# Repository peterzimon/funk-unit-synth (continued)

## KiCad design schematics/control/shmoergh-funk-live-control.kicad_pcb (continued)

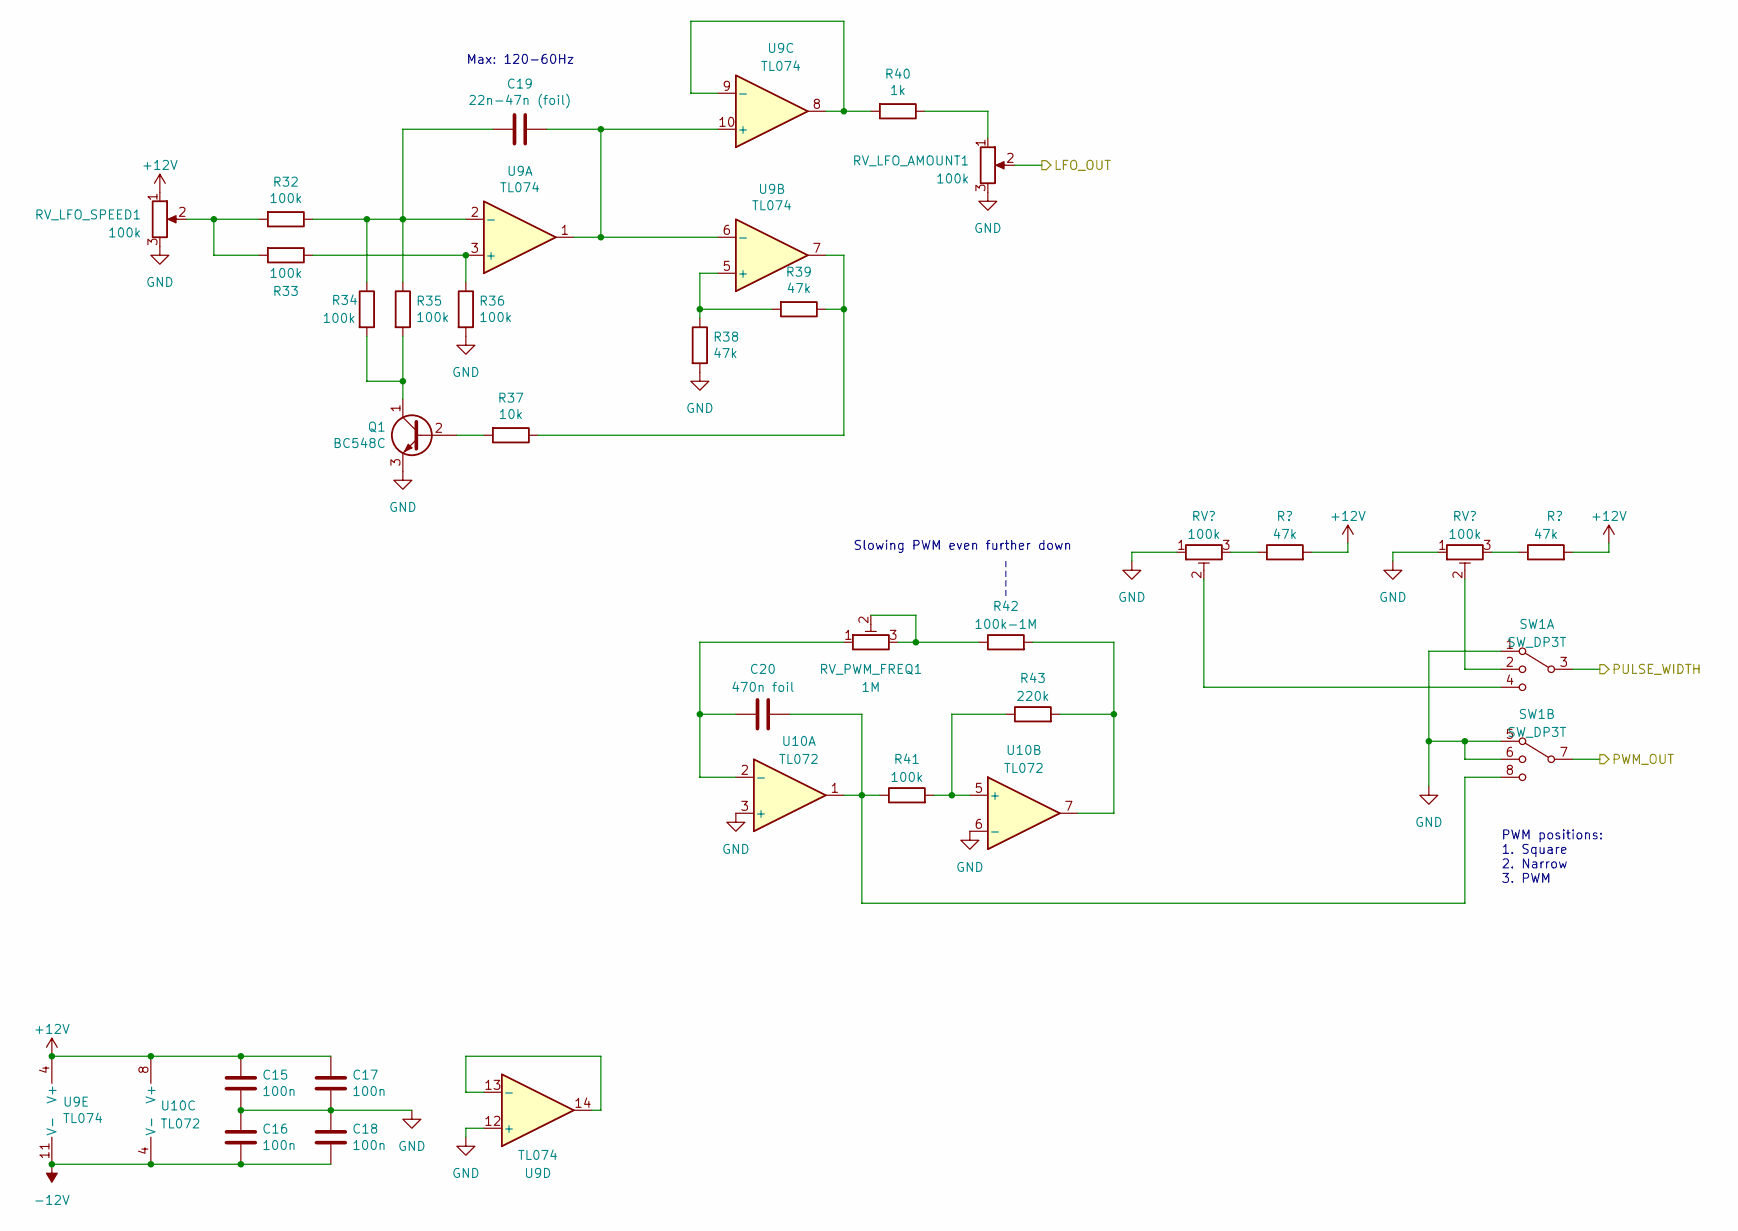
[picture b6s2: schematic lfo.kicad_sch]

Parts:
C15, C16, C17, C18: 100n; C_Disc_D3.0mm_W2.0mm_P2.50mm
C19: 22n-47n (foil); C_Rect_L7.0mm_W3.5mm_P5.00mm
C20: 470n foil; C_Rect_L7.0mm_W3.5mm_P5.00mm
Q1: BC548C; TO-92_Inline_Wide
R32, R33, R34, R35, R36, R41: 100k; R_Axial_DIN0207_L6.3mm_D2.5mm_P7.62mm_Horizontal
R37: 10k; R_Axial_DIN0207_L6.3mm_D2.5mm_P7.62mm_Horizontal
R38, R39, R44, R45: 47k; R_Axial_DIN0207_L6.3mm_D2.5mm_P7.62mm_Horizontal
R40: 1k; R_Axial_DIN0207_L6.3mm_D2.5mm_P7.62mm_Horizontal
R42: 100k-1M; R_Axial_DIN0207_L6.3mm_D2.5mm_P7.62mm_Horizontal
R43: 220k; R_Axial_DIN0207_L6.3mm_D2.5mm_P7.62mm_Horizontal
RV_LFO_AMOUNT1: 100k; NSL25_01x03_Vertical
RV_LFO_SPEED1: 100k; NSL25_01x03_Vertical
RV_NARROW_BIAS1: 100k; Potentiometer_Runtron_RM-065_Vertical
RV_PWM_BIAS1: 100k; Potentiometer_Runtron_RM-065_Vertical
RV_PWM_FREQ1: 1M; Potentiometer_Runtron_RM-065_Vertical
SW1: SW_DP3T; NSL25_01x08_Vertical
U9: TL074; DIP-14_W7.62mm_LongPads
U10: TL072; DIP-8_W7.62mm_LongPads

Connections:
-12V: C16.2, C18.2, U9.11 (V-), U10.4 (V-); also elsewhere on the board
unnamed: Q1.2 (B), R37.2
unnamed: Q1.1 (C), R34.2, R35.2
unnamed: R32.2, R33.2, RV_LFO_SPEED1.2
unnamed: R37.1, R39.1, U9.7
unnamed: R40.1, RV_LFO_AMOUNT1.1
unnamed: R42.1, RV_PWM_FREQ1.2, RV_PWM_FREQ1.3
unnamed: R42.2, R43.2, U10.7
unnamed: R44.1, RV_PWM_BIAS1.3
unnamed: R45.1, RV_NARROW_BIAS1.3
unnamed: R33.1, R36.1, U9.3 (+)
unnamed: C19.2, R32.1, R34.1, R35.1, U9.2 (-)
unnamed: R38.1, R39.2, U9.5 (+)
unnamed: C19.1, U9.1, U9.6 (-), U9.10 (+)
unnamed: R40.2, U9.8, U9.9 (-)
unnamed: U9.13 (-), U9.14
unnamed: C20.1, RV_PWM_FREQ1.1, U10.2 (-)
unnamed: R41.2, R43.1, U10.5 (+)
PWM_LFO: C20.2, R41.1, SW1.8, U10.1; also elsewhere on the board
PWM_LFO_BIAS: RV_PWM_BIAS1.2, SW1.4; also elsewhere on the board
PWM_NARROW_BIAS: RV_NARROW_BIAS1.2, SW1.2; also elsewhere on the board

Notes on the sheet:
Max: 120-60Hz
PWM positions: 1. Square 2. Narrow 3. PWM
Slowing PWM even further down

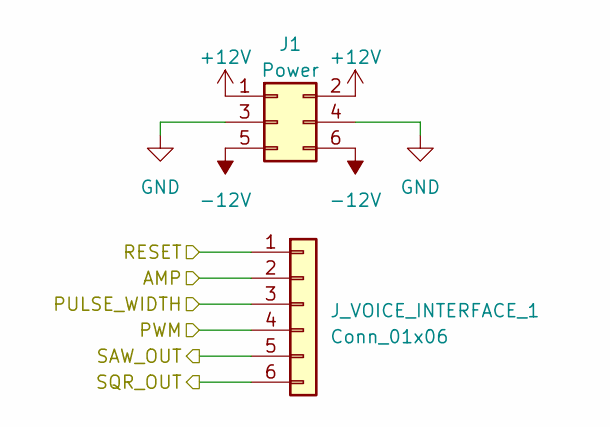
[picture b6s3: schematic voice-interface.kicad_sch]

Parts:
J1: Power; PinHeader_2x03_P2.54mm_Vertical
J_VOICE_INTERFACE_1: Conn_01x06; PinHeader_1x06_P2.54mm_Vertical

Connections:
-12V: J1.5, J1.6; also elsewhere on the board
/Digital/AMP_1: J_VOICE_INTERFACE_1.2; also elsewhere on the board
/Digital/RESET_1: J_VOICE_INTERFACE_1.1; also elsewhere on the board
/LFO + PWM/PULSE_WIDTH: J_VOICE_INTERFACE_1.3; also elsewhere on the board
/LFO + PWM/PWM_OUT: J_VOICE_INTERFACE_1.4; also elsewhere on the board
/Mixer/SAW_1_IN: J_VOICE_INTERFACE_1.5; also elsewhere on the board
/Mixer/SQR_1_IN: J_VOICE_INTERFACE_1.6; also elsewhere on the board

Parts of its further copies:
J2, J3, J4, J5, J6: Power; PinHeader_2x03_P2.54mm_Vertical
J_VOICE_INTERFACE_2, J_VOICE_INTERFACE_3, J_VOICE_INTERFACE_4, J_VOICE_INTERFACE_5, J_VOICE_INTERFACE_6: Conn_01x06; PinHeader_1x06_P2.54mm_Vertical

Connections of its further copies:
-12V: J2.5, J2.6, J3.5, J3.6, J4.5, J4.6, J5.5, J5.6, J6.5, J6.6; also elsewhere on the board
/Digital/AMP_2: J_VOICE_INTERFACE_2.2; also elsewhere on the board
/Digital/AMP_3: J_VOICE_INTERFACE_3.2; also elsewhere on the board
/Digital/AMP_4: J_VOICE_INTERFACE_4.2; also elsewhere on the board
/Digital/AMP_5: J_VOICE_INTERFACE_5.2; also elsewhere on the board
/Digital/AMP_6: J_VOICE_INTERFACE_6.2; also elsewhere on the board
/Digital/RESET_2: J_VOICE_INTERFACE_2.1; also elsewhere on the board
/Digital/RESET_3: J_VOICE_INTERFACE_3.1; also elsewhere on the board
/Digital/RESET_4: J_VOICE_INTERFACE_4.1; also elsewhere on the board
/Digital/RESET_5: J_VOICE_INTERFACE_5.1; also elsewhere on the board
/Digital/RESET_6: J_VOICE_INTERFACE_6.1; also elsewhere on the board
/LFO + PWM/PULSE_WIDTH: J_VOICE_INTERFACE_2.3, J_VOICE_INTERFACE_3.3, J_VOICE_INTERFACE_4.3, J_VOICE_INTERFACE_5.3, J_VOICE_INTERFACE_6.3; also elsewhere on the board
/LFO + PWM/PWM_OUT: J_VOICE_INTERFACE_2.4, J_VOICE_INTERFACE_3.4, J_VOICE_INTERFACE_4.4, J_VOICE_INTERFACE_5.4, J_VOICE_INTERFACE_6.4; also elsewhere on the board
/Mixer/SAW_2_IN: J_VOICE_INTERFACE_2.5; also elsewhere on the board
/Mixer/SAW_3_IN: J_VOICE_INTERFACE_3.5; also elsewhere on the board
/Mixer/SAW_4_IN: J_VOICE_INTERFACE_4.5; also elsewhere on the board
/Mixer/SAW_5_IN: J_VOICE_INTERFACE_5.5; also elsewhere on the board
/Mixer/SAW_6_IN: J_VOICE_INTERFACE_6.5; also elsewhere on the board
/Mixer/SQR_2_IN: J_VOICE_INTERFACE_2.6; also elsewhere on the board
/Mixer/SQR_3_IN: J_VOICE_INTERFACE_3.6; also elsewhere on the board
/Mixer/SQR_4_IN: J_VOICE_INTERFACE_4.6; also elsewhere on the board
/Mixer/SQR_5_IN: J_VOICE_INTERFACE_5.6; also elsewhere on the board
/Mixer/SQR_6_IN: J_VOICE_INTERFACE_6.6; also elsewhere on the board

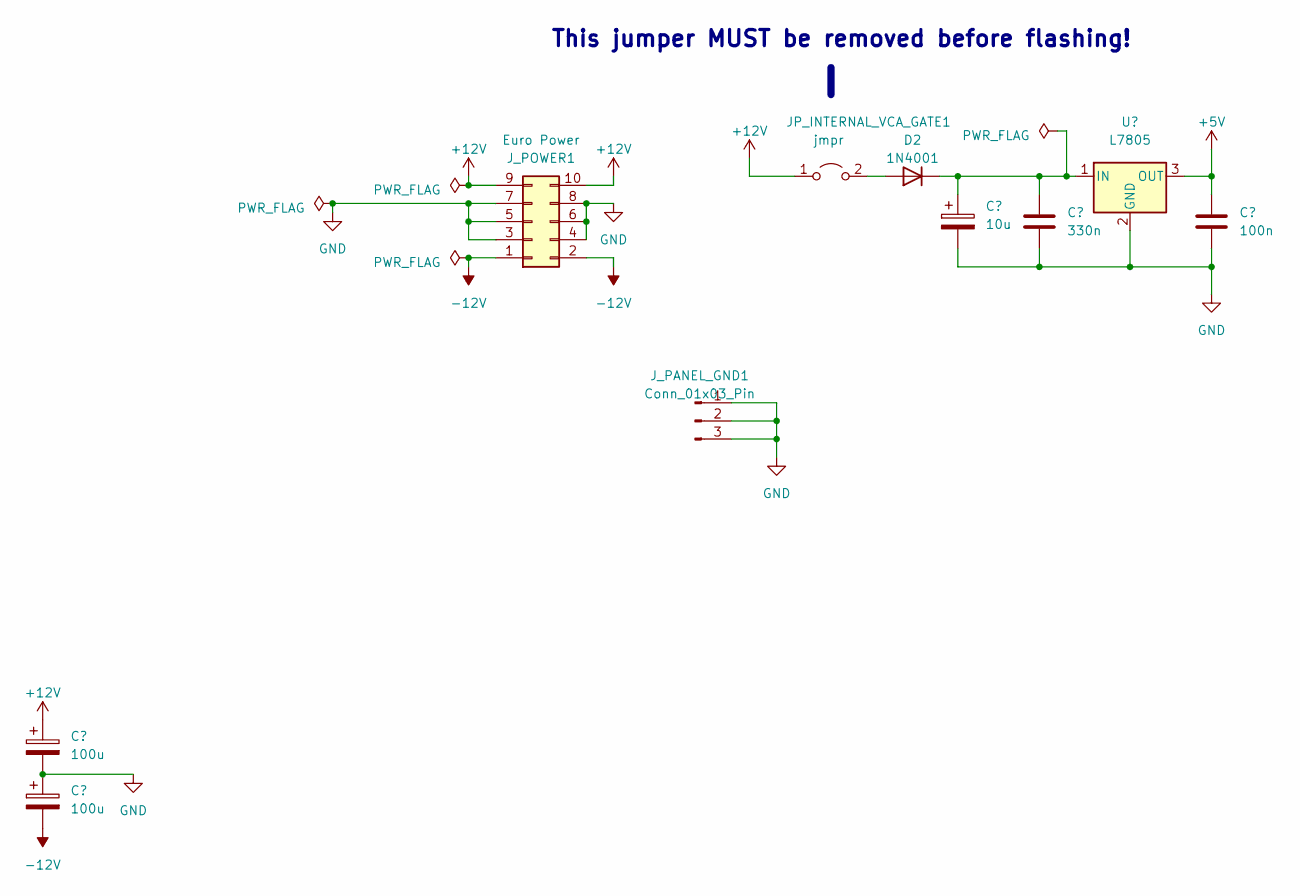
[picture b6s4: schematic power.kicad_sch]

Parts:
C21, C22: 100u; CP_Radial_D6.3mm_P2.50mm
C23: 10u; CP_Radial_D6.3mm_P2.50mm
C24: 330n; C_Disc_D3.0mm_W2.0mm_P2.50mm
C25: 100n; C_Disc_D3.0mm_W2.0mm_P2.50mm
D2: 1N4001; D_DO-41_SOD81_P7.62mm_Horizontal
JP_INTERNAL_VCA_GATE1: jmpr; Jumper_P2.54mm_D0.7mm
J_PANEL_GND1: Conn_01x03_Pin; NSL25_01x03_Vertical
J_POWER1: Euro Power; IDC-Header_2x05_P2.54mm_Vertical
U11: L7805; TO-220-3_Vertical

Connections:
+5V: C25.1, U11.3 (OUT); also elsewhere on the board
-12V: C22.2, J_POWER1.1, J_POWER1.2; also elsewhere on the board
unnamed: C23.1, C24.1, D2.1 (K), U11.1 (IN)

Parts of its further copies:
JP_MCU_EXT_PWR2: jmpr; Jumper_P2.54mm_D0.7mm

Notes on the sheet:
This jumper MUST be removed before flashing!

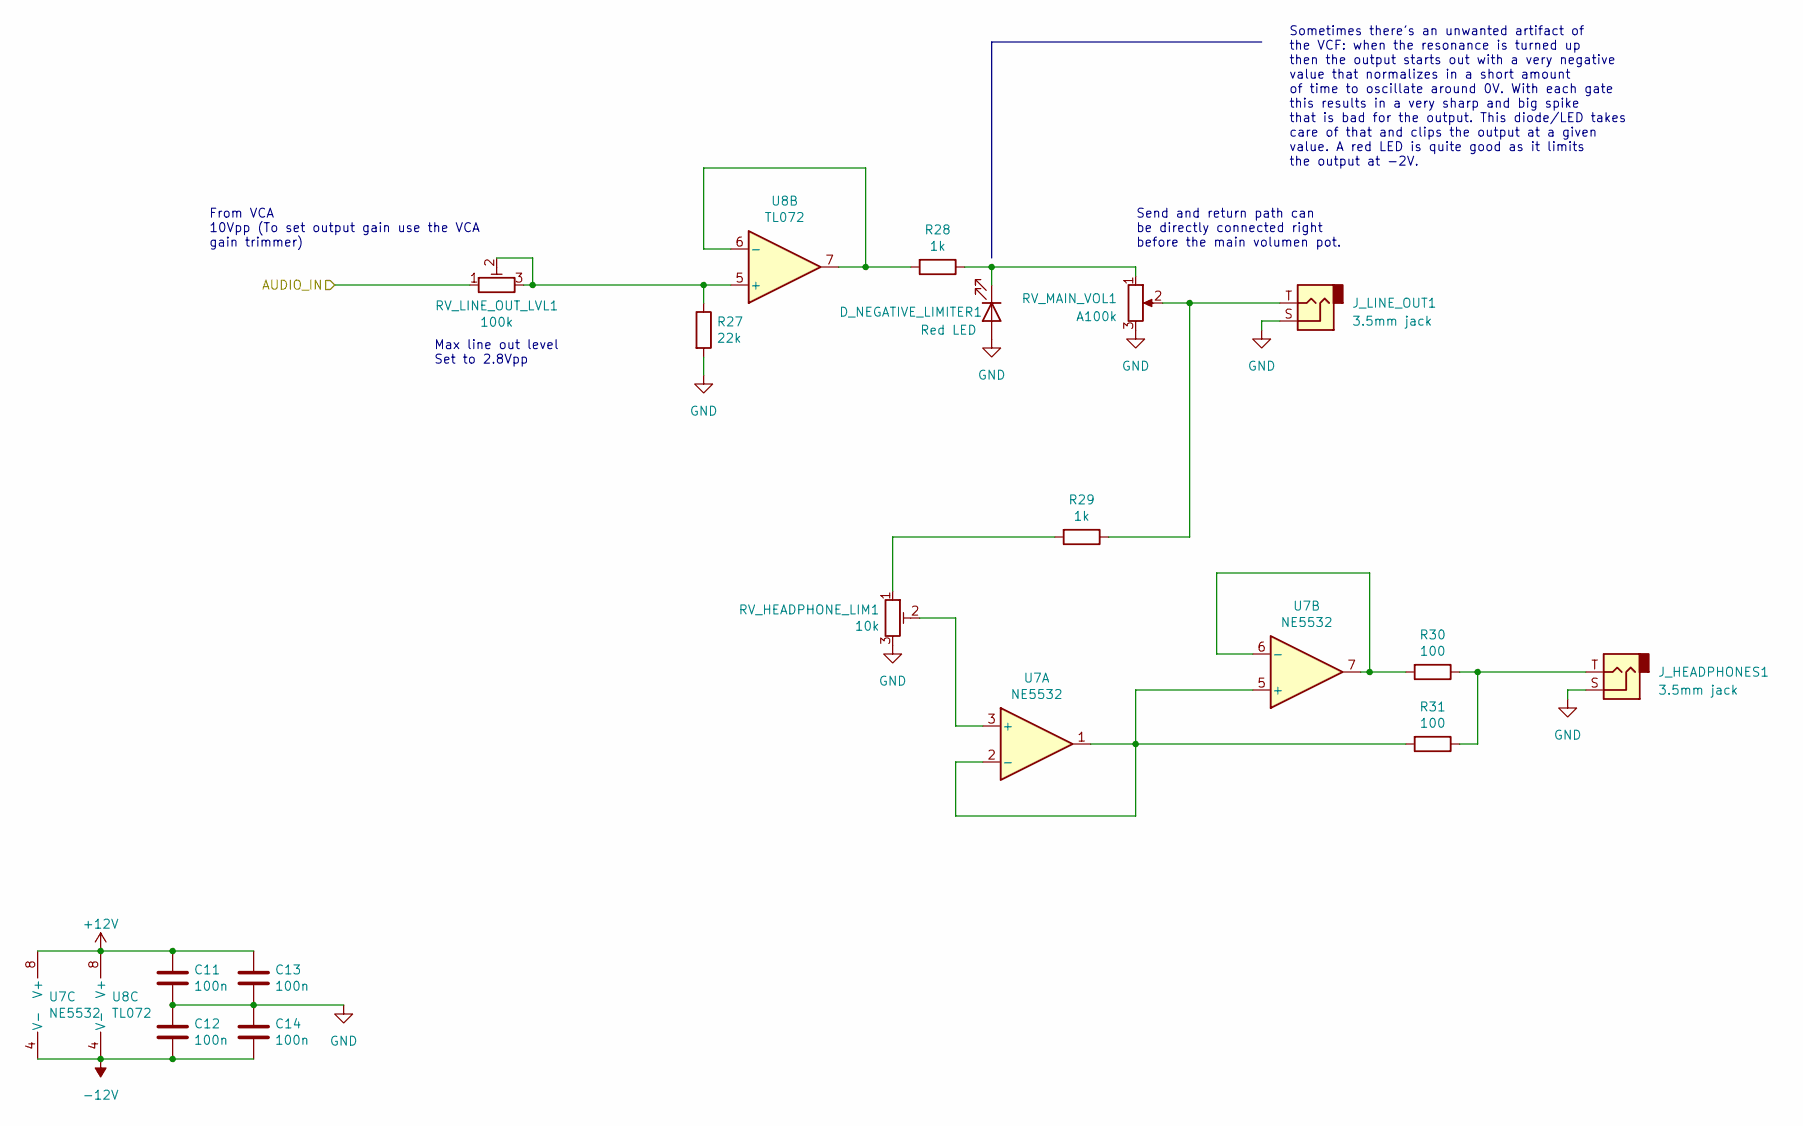
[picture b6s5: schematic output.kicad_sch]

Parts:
C11, C12, C13, C14: 100n; C_Disc_D3.0mm_W2.0mm_P2.50mm
D_NEGATIVE_LIMITER1: Red LED; LED_D5.0mm
J_HEADPHONES1: 3.5mm jack; NSL25_01x02_Vertical-AudioJack-TS
J_LINE_OUT1: 3.5mm jack; NSL25_01x02_Vertical-AudioJack-TS
R27: 22k; R_Axial_DIN0207_L6.3mm_D2.5mm_P7.62mm_Horizontal
R28, R29: 1k; R_Axial_DIN0207_L6.3mm_D2.5mm_P7.62mm_Horizontal
R30, R31: 100; R_Axial_DIN0207_L6.3mm_D2.5mm_P7.62mm_Horizontal
RV_HEADPHONE_LIM1: 10k; Potentiometer_Runtron_RM-065_Vertical
RV_LINE_OUT_LVL1: 100k; Potentiometer_Runtron_RM-065_Vertical
RV_MAIN_VOL1: A100k; NSL25_01x03_Vertical
U7: NE5532; DIP-8_W7.62mm_LongPads
U8: TL072; DIP-8_W7.62mm_LongPads

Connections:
-12V: C12.2, C14.2, U7.4 (V-), U8.4 (V-); also elsewhere on the board
/Output/AUDIO_IN: RV_LINE_OUT_LVL1.1; also elsewhere on the board
unnamed: D_NEGATIVE_LIMITER1.1 (K), R28.1, RV_MAIN_VOL1.1
unnamed: J_HEADPHONES1.T, R30.1, R31.1
unnamed: J_LINE_OUT1.T, R29.1, RV_MAIN_VOL1.2
unnamed: R29.2, RV_HEADPHONE_LIM1.1
unnamed: RV_HEADPHONE_LIM1.2, U7.3 (+)
unnamed: R31.2, U7.1, U7.2 (-), U7.5 (+)
unnamed: R30.2, U7.6 (-), U7.7
unnamed: R27.1, RV_LINE_OUT_LVL1.2, RV_LINE_OUT_LVL1.3, U8.5 (+)
unnamed: R28.2, U8.6 (-), U8.7

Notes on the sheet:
Sometimes there's an unwanted artifact of the VCF: when the resonance is turned up then the output starts out with a very negative value that normalizes in a short amount of time to oscillate around 0V. With each gate this results in a very sharp and big spike that is bad for the output. This diode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
Send and return path can be directly connected right before the main volumen pot.
Max line out level Set to 2.8Vpp
From VCA 10Vpp (To set output gain use the VCA gain trimmer)

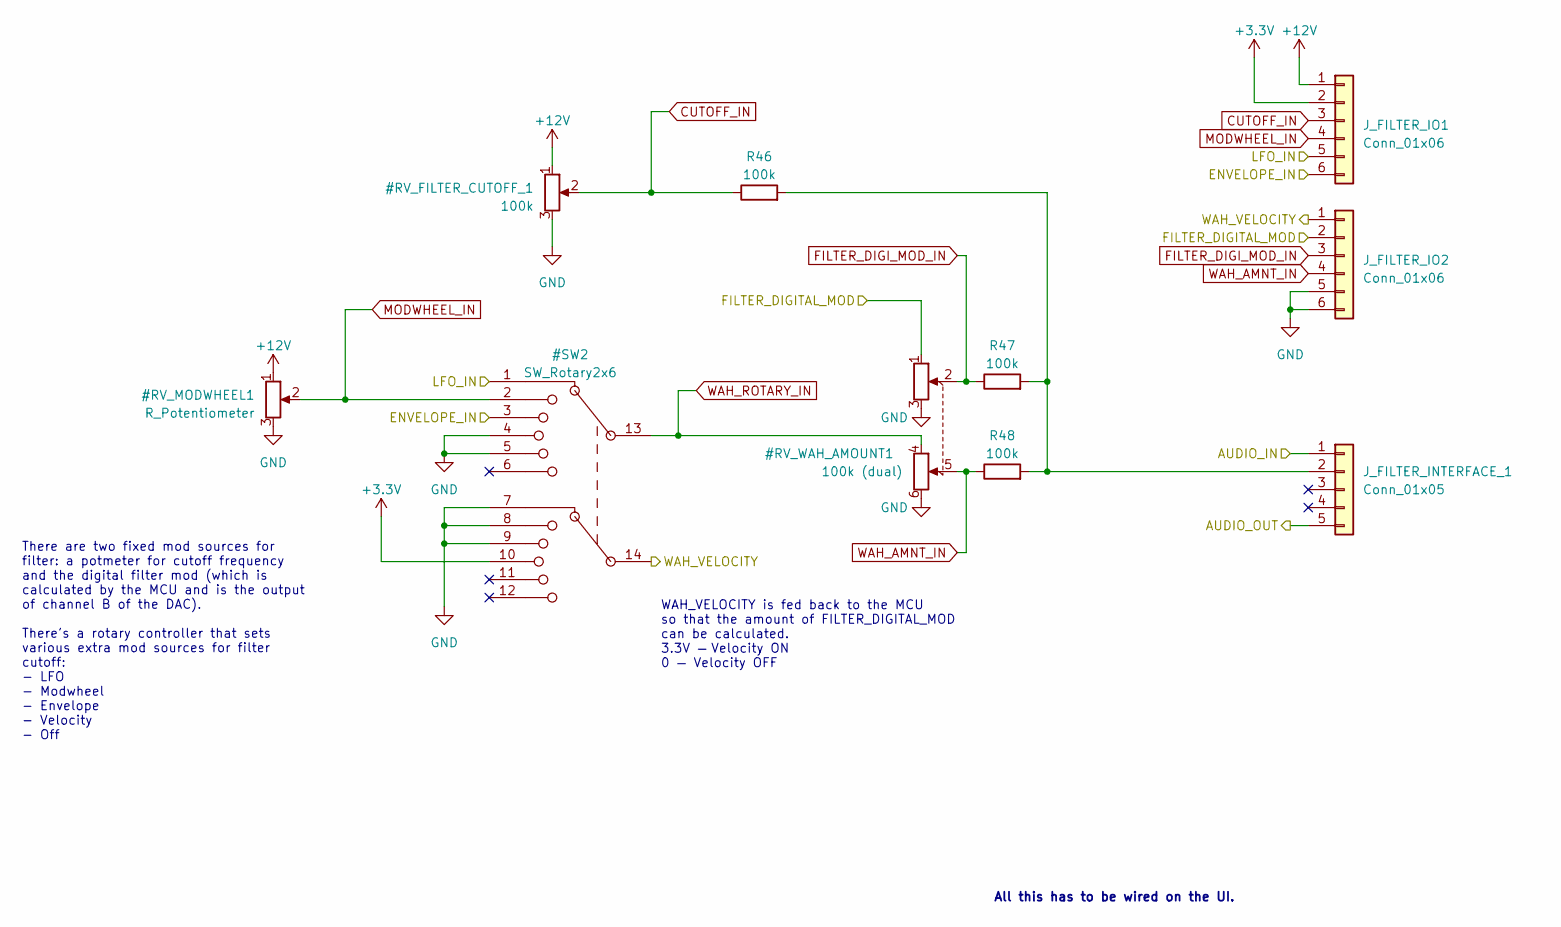
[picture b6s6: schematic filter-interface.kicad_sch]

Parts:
J_FILTER_INTERFACE_1: Conn_01x05; NSL25_01x05_Vertical
J_FILTER_IO1, J_FILTER_IO2: Conn_01x06; NSL25_01x06_Vertical
R46, R47, R48: 100k; R_Axial_DIN0207_L6.3mm_D2.5mm_P7.62mm_Horizontal

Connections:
/Filter Interface/AUDIO_IN: J_FILTER_INTERFACE_1.1; also elsewhere on the board
/Filter Interface/AUDIO_OUT: J_FILTER_INTERFACE_1.5; also elsewhere on the board
unnamed: J_FILTER_INTERFACE_1.2, R46.2, R47.2, R48.2

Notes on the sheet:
WAH_VELOCITY is fed back to the MCU so that the amount of FILTER_DIGITAL_MOD can be calculated. 3.3V — Velocity ON 0 — Velocity OFF
There are two fixed mod sources for filter: a potmeter for cutoff frequency and the digital filter mod (which is calculated by the MCU and is the output of channel B of the DAC). There's a rotary controller that sets various extra mod sources for filter cutoff: - LFO - Modwheel - Envelope - Velocit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
All this has to be wired on the UI.

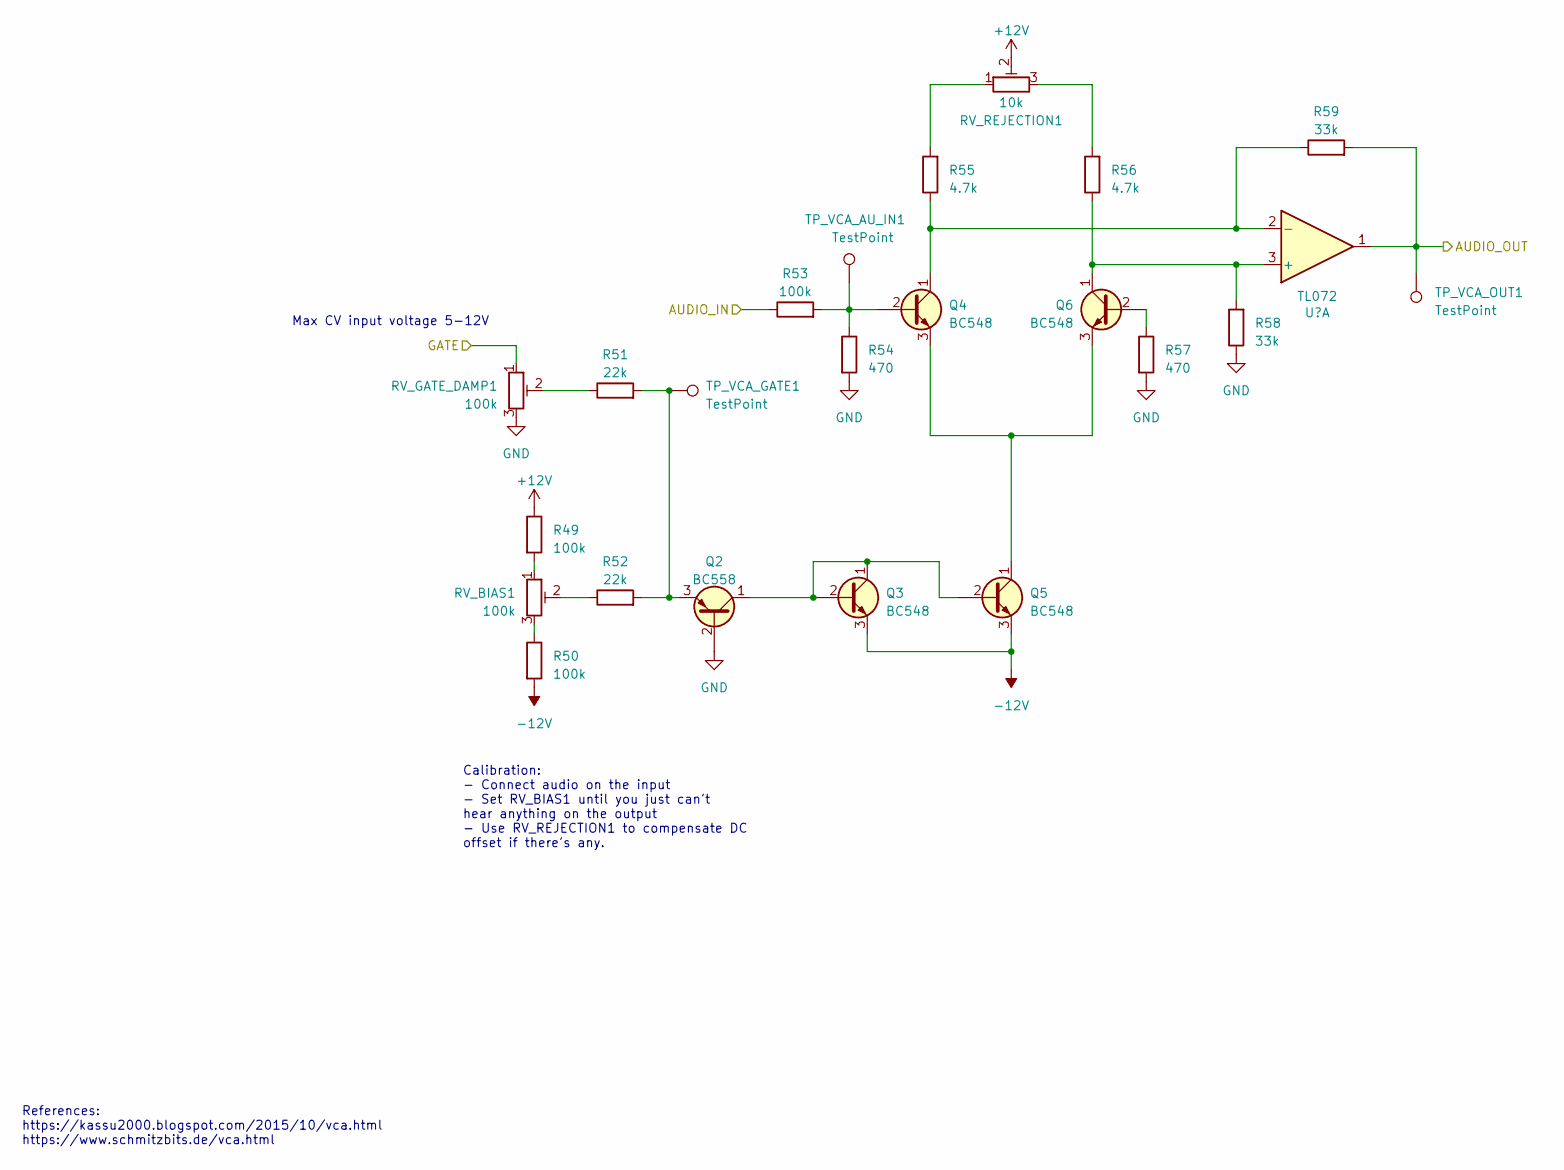
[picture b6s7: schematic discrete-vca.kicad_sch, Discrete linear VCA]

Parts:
Q2: BC558
Q3, Q4, Q5, Q6: BC548
R49, R50, R53: 100k
R51, R52: 22k
R54, R57: 470
R55, R56: 4.7k
R58, R59: 33k
RV_BIAS1: 100k
RV_GATE_DAMP1: 100k
RV_REJECTION1: 10k
TP_VCA_AU_IN1: TestPoint
TP_VCA_GATE1: TestPoint
TP_VCA_OUT1: TestPoint
U8: TL072

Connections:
-12V: Q3.3 (E), Q5.3 (E), R50.2; also elsewhere on the board
/VCA (Internal)/AUDIO_IN: R53.1; also elsewhere on the board
/VCA (Internal)/AUDIO_OUT: R59.2, TP_VCA_OUT1.1, U8.1; also elsewhere on the board
unnamed: Q2.1 (C), Q3.1 (C), Q3.2 (B), Q5.2 (B)
unnamed: Q2.3 (E), R51.2, R52.2, TP_VCA_GATE1.1
unnamed: Q4.2 (B), R53.2, R54.1, TP_VCA_AU_IN1.1
unnamed: Q4.1 (C), R55.1, R59.1, U8.2 (-)
unnamed: Q4.3 (E), Q5.1 (C), Q6.3 (E)
unnamed: Q6.2 (B), R57.1
unnamed: Q6.1 (C), R56.1, R58.2, U8.3 (+)
unnamed 71: R49.2, RV_BIAS1.1; also elsewhere on the board
unnamed 72: R50.1, RV_BIAS1.3; also elsewhere on the board
unnamed: R51.1, RV_GATE_DAMP1.2
unnamed 74: R52.1, RV_BIAS1.2; also elsewhere on the board
unnamed: R55.2, RV_REJECTION1.1
unnamed: R56.2, RV_REJECTION1.3

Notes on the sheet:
References: https://kassu2000.blogspot.com/2015/10/vca.html https://www.schmitzbits.de/vca.html
Max CV input voltage 5-12V
Calibration: - Connect audio on the input - Set RV_BIAS1 until you just can't hear anything on the output - Use RV_REJECTION1 to compensate DC offset if there's any.

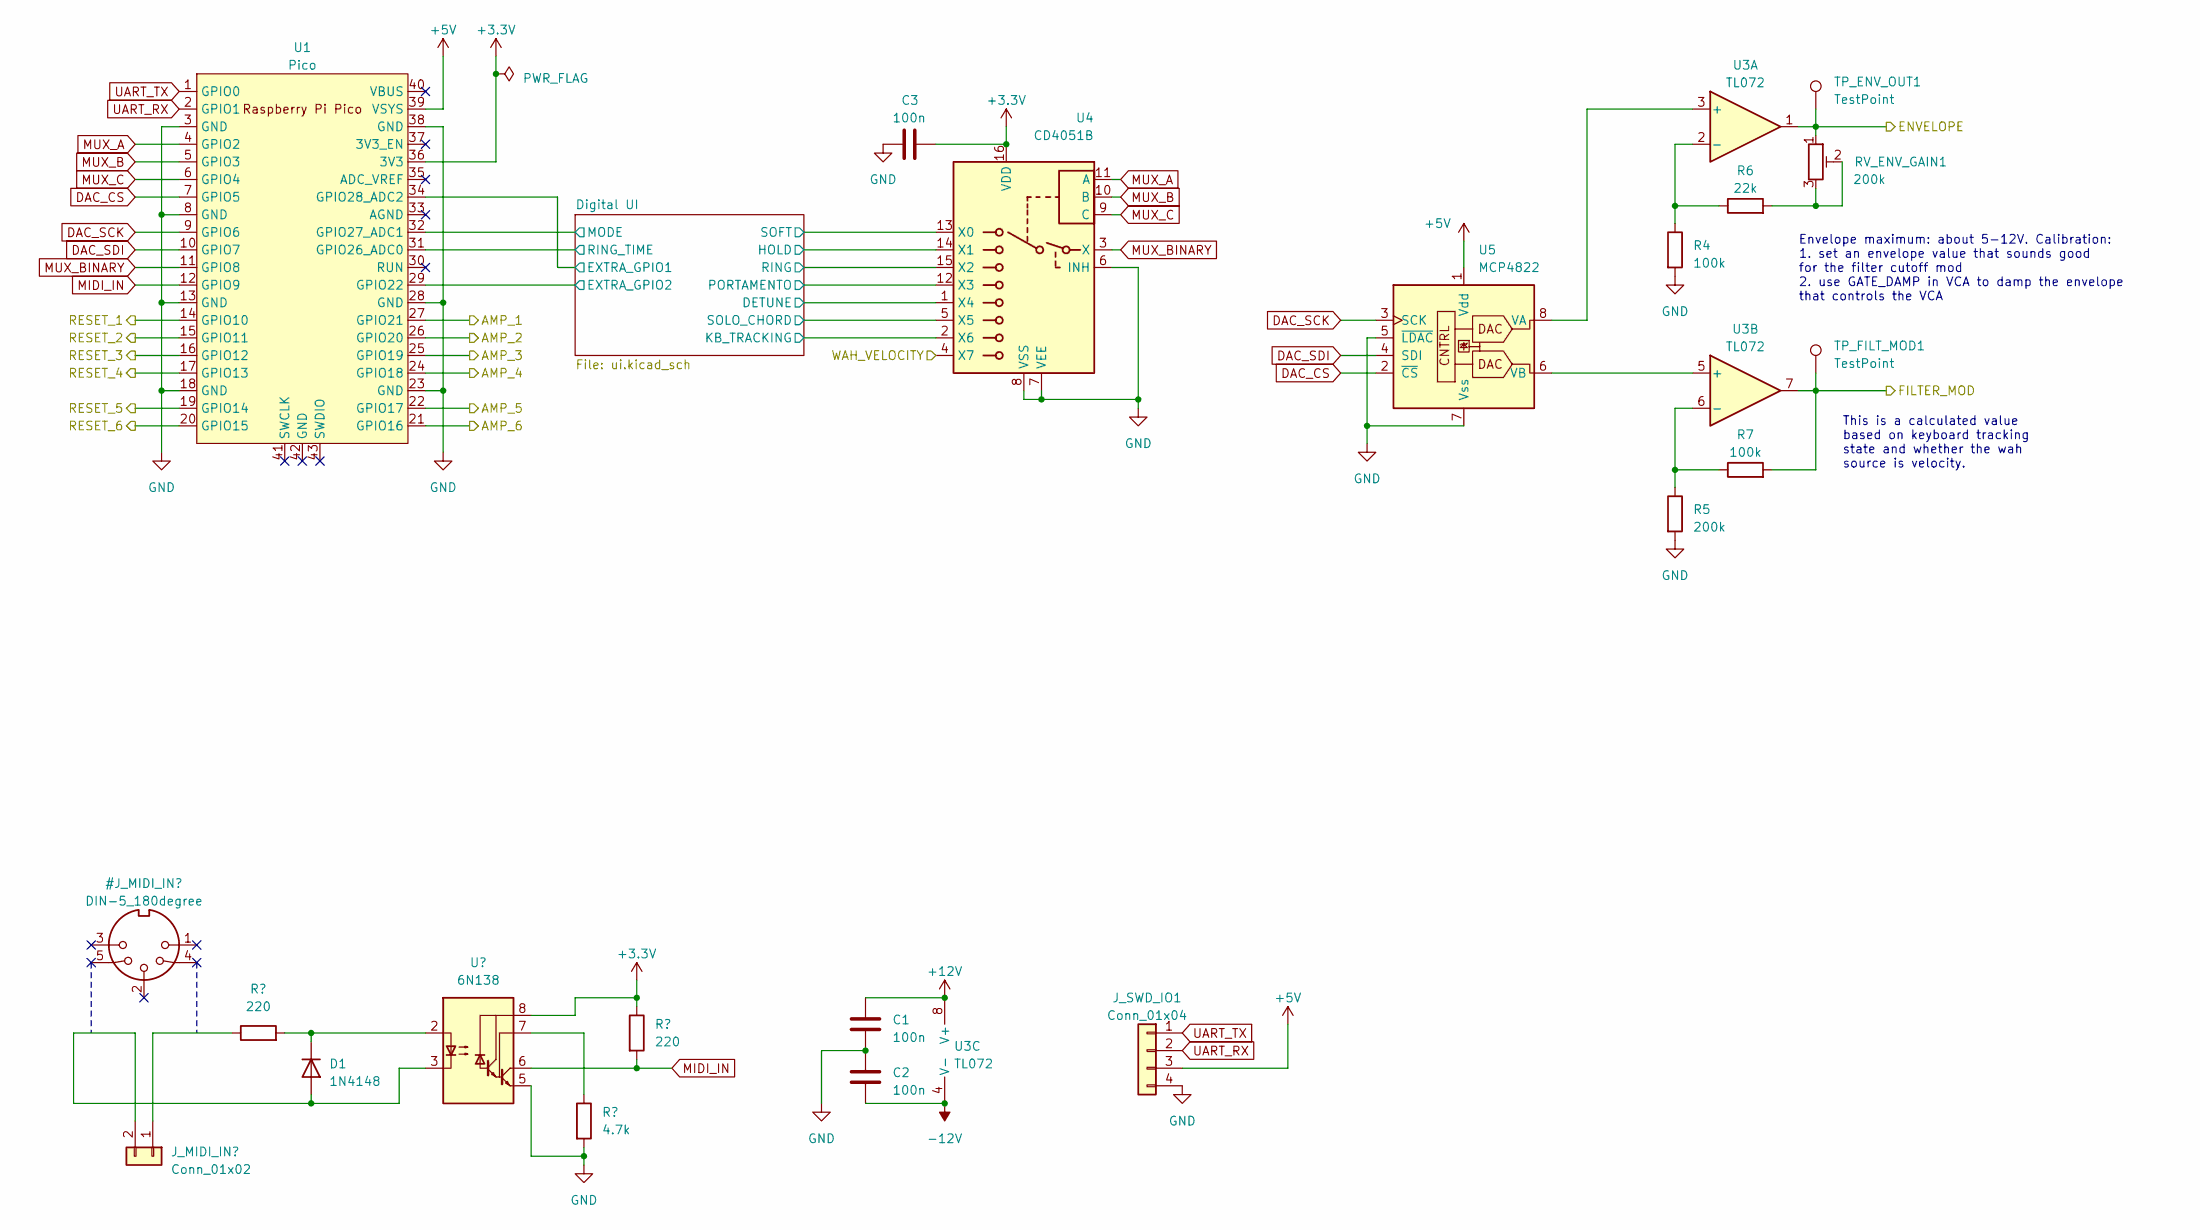
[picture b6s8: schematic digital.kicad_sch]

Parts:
C1, C2, C3: 100n; C_Disc_D3.0mm_W2.0mm_P2.50mm
D1: 1N4148; D_DO-35_SOD27_P7.62mm_Horizontal
J_MIDI_IN1: Conn_01x02; NSL25_01x02_Vertical
J_SWD_IO1: Conn_01x04; NSL25_01x04_Vertical
R1, R3: 220; R_Axial_DIN0207_L6.3mm_D2.5mm_P7.62mm_Horizontal
R2: 4.7k; R_Axial_DIN0207_L6.3mm_D2.5mm_P7.62mm_Horizontal
R4, R7: 100k; R_Axial_DIN0207_L6.3mm_D2.5mm_P7.62mm_Horizontal
R5: 200k; R_Axial_DIN0207_L6.3mm_D2.5mm_P7.62mm_Horizontal
R6: 22k; R_Axial_DIN0207_L6.3mm_D2.5mm_P7.62mm_Horizontal
RV_ENV_GAIN1: 200k; Potentiometer_Runtron_RM-065_Vertical
TP_ENV_OUT1: TestPoint; TestPoint_THTPad_D2.0mm_Drill1.0mm
TP_FILT_MOD1: TestPoint; TestPoint_THTPad_D2.0mm_Drill1.0mm
U1: Pico; RPi_Pico_SMD_TH
U2: 6N138; DIP-8_W7.62mm_LongPads
U3: TL072; DIP-8_W7.62mm_LongPads
U4: CD4051B; DIP-16_W7.62mm_LongPads
U5: MCP4822; DIP-8_W7.62mm_LongPads

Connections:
+5V: J_SWD_IO1.3, U1.39 (VSYS), U5.1 (Vdd); also elsewhere on the board
-12V: C2.2, U3.4 (V-); also elsewhere on the board
/Digital/AMP_1: U1.27 (GPIO21); also elsewhere on the board
/Digital/AMP_2: U1.26 (GPIO20); also elsewhere on the board
/Digital/AMP_3: U1.25 (GPIO19); also elsewhere on the board
/Digital/AMP_4: U1.24 (GPIO18); also elsewhere on the board
/Digital/AMP_5: U1.22 (GPIO17); also elsewhere on the board
/Digital/AMP_6: U1.21 (GPIO16); also elsewhere on the board
/Digital/Digital UI/EXTRA_GPIO1: U1.34 (GPIO28_ADC2); also elsewhere on the board
/Digital/Digital UI/EXTRA_GPIO2: U1.29 (GPIO22); also elsewhere on the board
/Digital/RESET_1: U1.14 (GPIO10); also elsewhere on the board
/Digital/RESET_2: U1.15 (GPIO11); also elsewhere on the board
/Digital/RESET_3: U1.16 (GPIO12); also elsewhere on the board
/Digital/RESET_4: U1.17 (GPIO13); also elsewhere on the board
/Digital/RESET_5: U1.19 (GPIO14); also elsewhere on the board
/Digital/RESET_6: U1.20 (GPIO15); also elsewhere on the board
DAC_CS: U1.7 (GPIO5), U5.2 (~CS)
DAC_SCK: U1.9 (GPIO6), U5.3 (SCK)
DAC_SDI: U1.10 (GPIO7), U5.4 (SDI)
MIDI_IN: R3.2, U1.12 (GPIO9), U2.6 (VO2)
MUX_A: U1.4 (GPIO2), U4.11 (A)
MUX_B: U1.5 (GPIO3), U4.10 (B)
MUX_BINARY: U1.11 (GPIO8), U4.3 (X)
MUX_C: U1.6 (GPIO4), U4.9 (C)
unnamed: D1.2 (A), J_MIDI_IN1.2, U2.3 (C2)
unnamed: D1.1 (K), R1.2, U2.2 (C1)
unnamed: J_MIDI_IN1.1, R1.1
unnamed: R6.2, RV_ENV_GAIN1.2, RV_ENV_GAIN1.3
unnamed: R2.1, U2.7 (VO1)
unnamed: U3.3 (+), U5.8 (VA)
unnamed: R4.1, R6.1, U3.2 (-)
unnamed: U3.5 (+), U5.6 (VB)
unnamed: R5.1, R7.1, U3.6 (-)
UART_RX: J_SWD_IO1.2, U1.2 (GPIO1)
UART_TX: J_SWD_IO1.1, U1.1 (GPIO0)

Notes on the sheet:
This is a calculated value based on keyboard tracking state and whether the wah source is velocity.
Envelope maximum: about 5-12V. Calibration: 1. set an envelope value that sounds good for the filter cutoff mod 2. use GATE_DAMP in VCA to damp the envelope that controls the VCA

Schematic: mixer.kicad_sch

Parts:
C4, C5, C6, C7: 22p; C_Disc_D3.0mm_W2.0mm_P2.50mm
C8: 470n (foil); C_Rect_L7.0mm_W3.5mm_P5.00mm
C9, C10: 100n; C_Disc_D3.0mm_W2.0mm_P2.50mm
R8, R9, R10, R11, R12, R13, R14, R15, R16, R17, R18, R19, R20, R21, R22, R23, R24, R25: 100k; R_Axial_DIN0207_L6.3mm_D2.5mm_P7.62mm_Horizontal
R26: 1M; R_Axial_DIN0207_L6.3mm_D2.5mm_P7.62mm_Horizontal
SW_WAVESHAPE1: SW_SPDT; NSL25_01x03_Vertical
TP_SAW_SUBMIX1: TestPoint; TestPoint_THTPad_D2.0mm_Drill1.0mm
TP_SQR_SUBMIX1: TestPoint; TestPoint_THTPad_D2.0mm_Drill1.0mm
U6: TL074; DIP-14_W7.62mm_LongPads

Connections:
-12V: C10.2, U6.11 (V-); also elsewhere on the board
/Filter Interface/AUDIO_IN: C8.2, R26.1; also elsewhere on the board
/Mixer/SAW_1_IN: R8.1; also elsewhere on the board
/Mixer/SAW_2_IN: R9.1; also elsewhere on the board
/Mixer/SAW_3_IN: R10.1; also elsewhere on the board
/Mixer/SAW_4_IN: R11.1; also elsewhere on the board
/Mixer/SAW_5_IN: R12.1; also elsewhere on the board
/Mixer/SAW_6_IN: R13.1; also elsewhere on the board
/Mixer/SQR_1_IN: R14.1; also elsewhere on the board
/Mixer/SQR_2_IN: R15.1; also elsewhere on the board
/Mixer/SQR_3_IN: R16.1; also elsewhere on the board
/Mixer/SQR_4_IN: R17.1; also elsewhere on the board
/Mixer/SQR_5_IN: R18.1; also elsewhere on the board
/Mixer/SQR_6_IN: R19.1; also elsewhere on the board
unnamed: C4.2, R20.2, R22.1, U6.1
unnamed: C5.2, R21.2, R23.1, U6.8
unnamed: C6.2, R24.2, SW_WAVESHAPE1.1 (A), TP_SAW_SUBMIX1.1, U6.7
unnamed: C8.1, SW_WAVESHAPE1.2 (B)
unnamed: C7.2, R25.2, SW_WAVESHAPE1.3 (C), TP_SQR_SUBMIX1.1, U6.14
unnamed: C4.1, R8.2, R9.2, R10.2, R11.2, R12.2, R13.2, R20.1, U6.2 (-)
unnamed: C6.1, R22.2, R24.1, U6.6 (-)
unnamed: C5.1, R14.2, R15.2, R16.2, R17.2, R18.2, R19.2, R21.1, U6.9 (-)
unnamed: C7.1, R23.2, R25.1, U6.13 (-)

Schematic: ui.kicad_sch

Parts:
J_UI1, J_UI2: Conn_01x06
R60, R61: 100k

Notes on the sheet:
Value voltages (GND, 3.3V and 1.5V) are connected with wires between switches. By default the [mux] input of the MCU is pulled up.

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
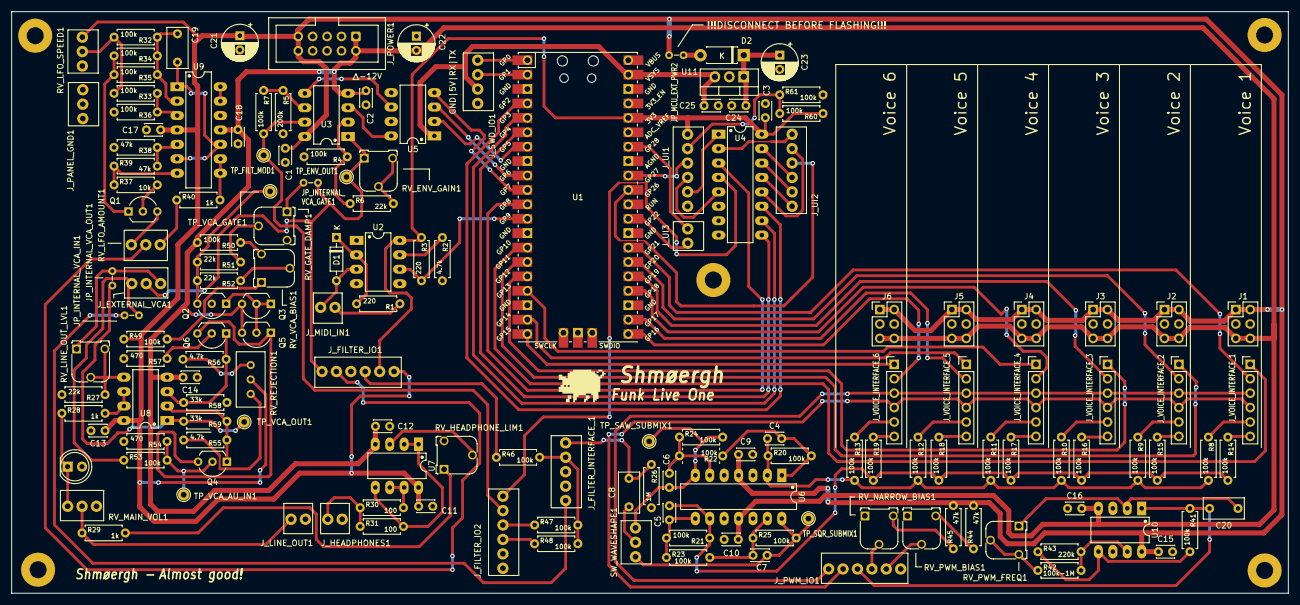
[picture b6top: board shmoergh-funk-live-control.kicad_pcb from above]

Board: 2 copper layers, 225.0 x 102.5 mm, 161 parts (0 on the bottom side), 129 nets.

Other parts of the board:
J_PWM_IO1: Conn_01x06; NSL25_01x06_Vertical
J_UI3: Conn_01x02; NSL25_01x02_Vertical
RV_VCA_BIAS1: 100k; Potentiometer_Runtron_RM-065_Vertical

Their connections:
/Digital/Digital UI/EXTRA_GPIO1: J_UI3.1; also elsewhere on the board
/Digital/Digital UI/EXTRA_GPIO2: J_UI3.2; also elsewhere on the board
/LFO + PWM/PULSE_WIDTH: J_PWM_IO1.1; also elsewhere on the board
/LFO + PWM/PWM_OUT: J_PWM_IO1.2; also elsewhere on the board
unnamed 71: RV_VCA_BIAS1.1; also elsewhere on the board
unnamed 72: RV_VCA_BIAS1.3; also elsewhere on the board
unnamed 74: RV_VCA_BIAS1.2; also elsewhere on the board
PWM_LFO: J_PWM_IO1.3; also elsewhere on the board
PWM_LFO_BIAS: J_PWM_IO1.5; also elsewhere on the board
PWM_NARROW_BIAS: J_PWM_IO1.4; also elsewhere on the board

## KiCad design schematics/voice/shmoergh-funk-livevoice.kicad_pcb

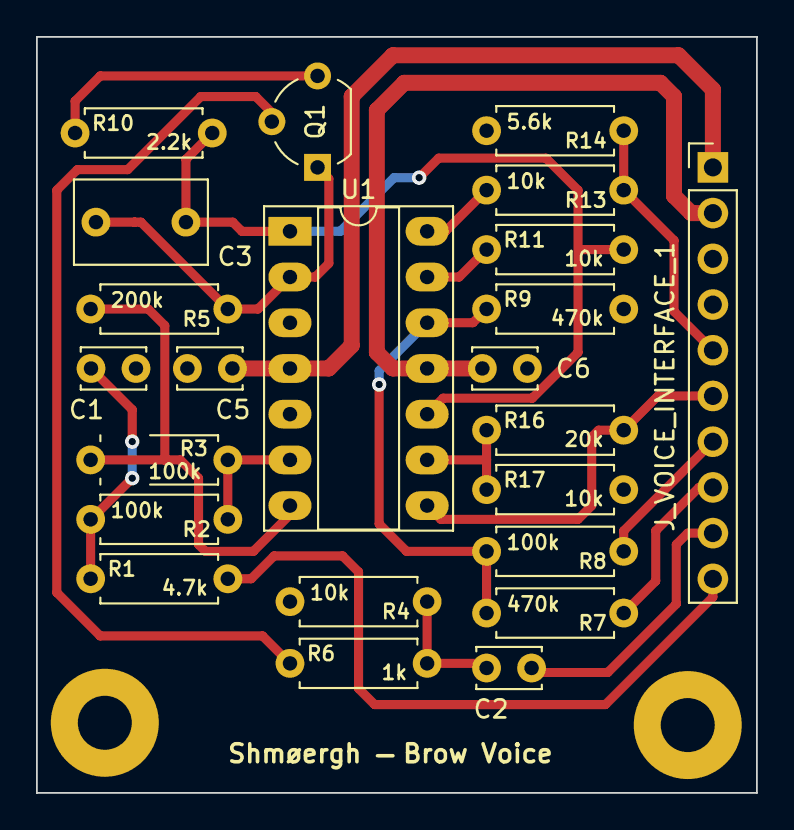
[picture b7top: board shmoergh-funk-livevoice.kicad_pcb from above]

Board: 2 copper layers, 40.0 x 42.0 mm, 25 parts (0 on the bottom side), 21 nets.

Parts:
C1, C5, C6: 100n; C_Disc_D3.4mm_W2.1mm_P2.50mm
C2: 270p; C_Disc_D3.4mm_W2.1mm_P2.50mm
C3: 1n (foil); C_Rect_L7.2mm_W4.5mm_P5.00mm_FKS2_FKP2_MKS2_MKP2
H1, H2: MountingHole; MountingHole_3mm_Pad
J_VOICE_INTERFACE_1: Conn_01x10; PinHeader_1x10_P2.54mm_Vertical
Q1: 2N3904; TO-92_Wide
R1: 4.7k; R_Axial_DIN0207_L6.3mm_D2.5mm_P7.62mm_Horizontal
R2, R3, R8: 100k; R_Axial_DIN0207_L6.3mm_D2.5mm_P7.62mm_Horizontal
R4, R11, R13, R17: 10k; R_Axial_DIN0207_L6.3mm_D2.5mm_P7.62mm_Horizontal
R5: 200k; R_Axial_DIN0207_L6.3mm_D2.5mm_P7.62mm_Horizontal
R6: 1k; R_Axial_DIN0207_L6.3mm_D2.5mm_P7.62mm_Horizontal
R7, R9: 470k; R_Axial_DIN0207_L6.3mm_D2.5mm_P7.62mm_Horizontal
R10: 2.2k; R_Axial_DIN0207_L6.3mm_D2.5mm_P7.62mm_Horizontal
R14: 5.6k; R_Axial_DIN0207_L6.3mm_D2.5mm_P7.62mm_Horizontal
R16: 20k; R_Axial_DIN0207_L6.3mm_D2.5mm_P7.62mm_Horizontal
U1: TL074; DIP-14_W7.62mm_Socket_LongPads

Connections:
+12V: C5.1, J_VOICE_INTERFACE_1.1, U1.4 (V+)
-12V: C6.2, J_VOICE_INTERFACE_1.2, U1.11 (V-)
AMP: J_VOICE_INTERFACE_1.10, R1.2
GND: C1.2, C5.2, C6.1, J_VOICE_INTERFACE_1.3, R4.2, R9.2, R14.2, R17.2, U1.3 (+), U1.5 (+)
unnamed: C1.1, R1.1, R2.2
unnamed: C2.1, R4.1, R6.2
unnamed: Q1.2 (B), R6.1
unnamed: Q1.3 (C), R10.1
unnamed: C3.2, Q1.1 (E), R5.1, U1.2 (-)
unnamed: R3.1, R5.2, U1.7
unnamed: R13.2, U1.14
unnamed: R2.1, R3.2, U1.6 (-)
unnamed: C3.1, R10.2, R11.2, U1.1, U1.10 (+)
unnamed: R16.1, R17.1, U1.9 (-)
unnamed: R7.2, R8.2, R9.1, U1.12 (+)
unnamed: R11.1, U1.13 (-)
PULSE_WIDTH: J_VOICE_INTERFACE_1.7, R8.1
PWM: J_VOICE_INTERFACE_1.8, R7.1
RESET: C2.2, J_VOICE_INTERFACE_1.9
SAW_OUT: J_VOICE_INTERFACE_1.6, R16.2, U1.8
SQR_OUT: J_VOICE_INTERFACE_1.5, R13.1, R14.1
